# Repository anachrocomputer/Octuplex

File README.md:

# Octuplex #

A 6502/6809 microcomputer in the shape of an octagon.

## Microprocessor ##

A choice of two classic 8-bit CPUs, the 6502 or the 6809.
The two chips have similar pinouts and are placed on the PCB overlapping.
Only one chip may be installed at a time.
Clock speed 2MHz in both cases,
with the 68B09 requiring a 4x clock input,
i.e. 8MHz.
The Hitachi 63B09 may also be fitted.

## Timer ##

The standard Motorola MC6840 timer chip.
Can generate interrupts and/or PWM signals.

## Parallel I/O ##

The standard 6522 parallel port chip.
Can generate interrupts.

Two handy little circuits for additional 8-bit I/O with minimal pin count: 74LS259 and 74LS251.
The 74LS259 is an unusual chip, an addressable latch.
It takes three address input pins and a single data input pin,
and has eight output pins.
The 74LS251 is an eight-input multiplexer with tri-state output.
The selector inputs are connected to three address pins,
while the output is connected to data bit D7.
The 6502's BIT instruction can read D7 directly into the sign flag,
which can be followed by BMI or BPL.

## Analog I/O ##

The classic Ferranti ZN428 8-bit DAC chip.

The classic Ferranti ZN448 b-bit ADC chip.
Although I'm not sure about this one due to its need for a negative supply rail.

## I2C Bus ##

Classic Philips PCF8584 I2C bus controller.
Can generate interrupts.

## Async Serial I/O ##

Rockwell R65C52 dual ACIA.
Can generate interrupts.

Motorola MC6850 with optocoupler for MIDI.
Can generate interrupts.

## Display ##

TBD, most likely an LED starburst display of some kind.

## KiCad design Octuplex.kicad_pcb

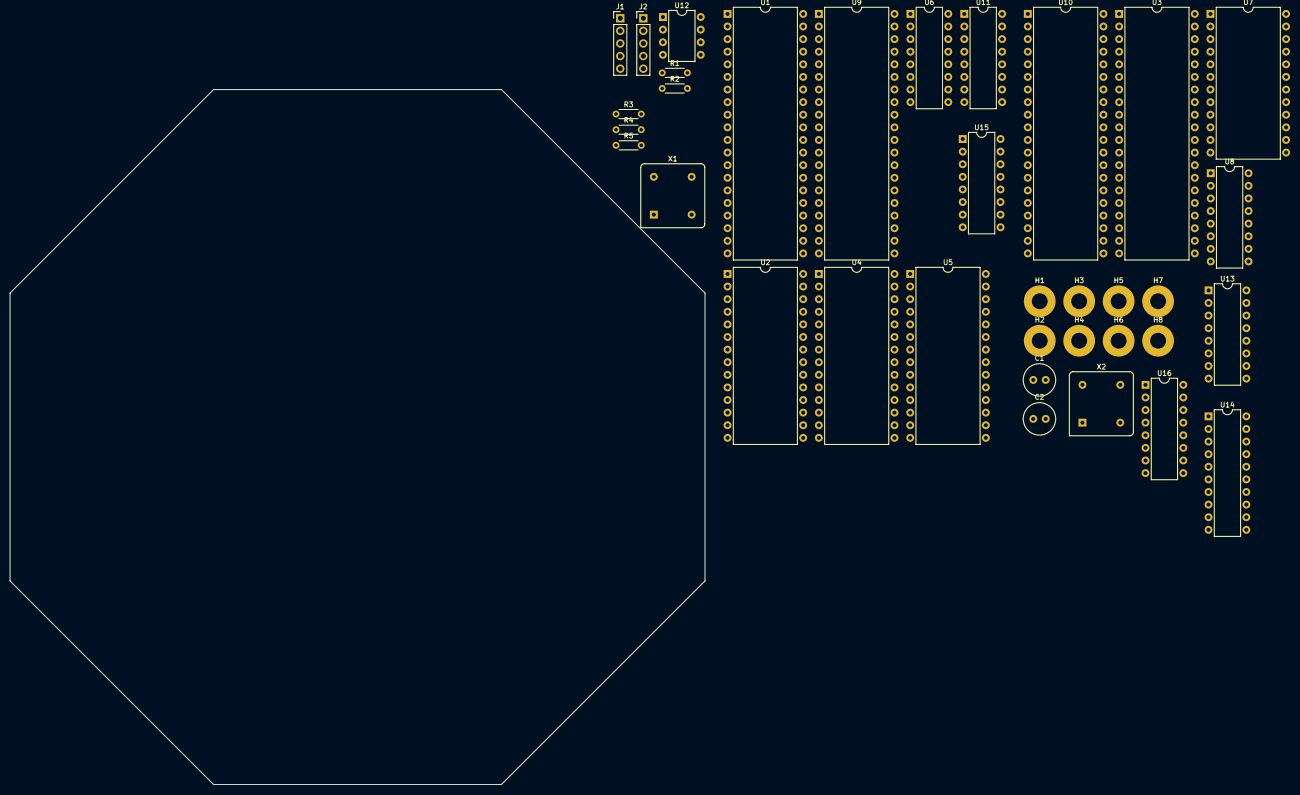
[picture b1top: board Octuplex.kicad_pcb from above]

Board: 2 copper layers, 140.0 x 140.0 mm, 35 parts (0 on the bottom side), 44 nets, no tracks yet.

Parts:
C1, C2: 0.1uF; C_Radial_D6.3mm_H5.0mm_P2.50mm
H1, H2, H3, H4, H5, H6, H7, H8: MountingHole_Pad; MountingHole_3.2mm_M3_Pad
J1, J2: DIN-5_180degree; PinHeader_1x05_P2.54mm_Vertical
R1: 220; R_Axial_DIN0204_L3.6mm_D1.6mm_P5.08mm_Horizontal
R2: 280; R_Axial_DIN0204_L3.6mm_D1.6mm_P5.08mm_Horizontal
R3, R4, R5: 10k; R_Axial_DIN0204_L3.6mm_D1.6mm_P5.08mm_Horizontal
U1: MC68B09; DIP-40_W15.24mm
U2: MC68B40; DIP-28_W15.24mm
U3: R65C52; DIP-40_W15.24mm
U4: 27128; DIP-28_W15.24mm
U5: HM62256BLP; DIP-28_W15.24mm
U6: 74LS139; DIP-16_W7.62mm
U7: MC68B50; DIP-24_W15.24mm
U8: 74LS259; DIP-16_W7.62mm
U9: M6502; DIP-40_W15.24mm
U10: R6522; DIP-40_W15.24mm
U11, U15: 74LS138; DIP-16_W7.62mm
U12: HCPL-2631; DIP-8_W7.62mm
U13: 74LS251; DIP-16_W7.62mm
U14: PCF8584; DIP-20_W7.62mm
U16: ZN428; DIP-16_W7.62mm
X1, X2: CXO_DIP8; Oscillator_DIP-8

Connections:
/E: U1.34 (E), U2.17 (E), U6.3 (A1), U7.14 (E), U9.39 (E), U10.25 (E), U11.6 (E3)
/Microprocessor/~IOSEL: U6.10 (O2), U11.4 (E1), U15.4 (E1)
/Microprocessor/~ROMCS: U4.20 (~CE), U6.9 (O3)
/Microprocessor/~TIMERCS: U2.15 (~CS0), U15.15 (O0)
/R/~W: U1.32 (R/~W), U2.13 (R/~W), U3.38 (R/~W), U6.2 (A0), U7.13 (R/~W), U9.34 (R/~W), U10.22 (R/~W), U11.1 (A0)
/a0: U1.8 (A0), U2.10 (RS0), U3.35 (RS0), U4.10 (A0), U5.10 (A0), U7.11 (RS), U8.1 (A0), U9.9 (A0), U10.38 (RS0), U13.11 (S0), U14.6 (A0)
/a1: U1.9 (A1), U2.11 (RS1), U3.36 (RS1), U4.9 (A1), U5.9 (A1), U8.2 (A1), U9.10 (A1), U10.37 (RS1), U13.10 (S1)
/a2: U1.10 (A2), U2.12 (RS2), U3.37 (RS2), U4.8 (A2), U5.8 (A2), U8.3 (A2), U9.11 (A2), U10.36 (RS2), U13.9 (S2)
/a3: U1.11 (A3), U4.7 (A3), U5.7 (A3), U9.12 (A3), U10.35 (RS3)
/a4: U1.12 (A4), U4.6 (A4), U5.6 (A4), U9.13 (A4)
/a5: U1.13 (A5), U4.5 (A5), U5.5 (A5), U9.14 (A5)
/a6: U1.14 (A6), U4.4 (A6), U5.4 (A6), U9.15 (A6)
/a7: U1.15 (A7), U4.3 (A7), U5.3 (A7), U9.16 (A7)
/a8: U1.16 (A8), U4.25 (A8), U5.25 (A8), U9.17 (A8)
/a9: U1.17 (A9), U4.24 (A9), U5.24 (A9), U9.18 (A9)
/a10: U1.18 (A10), U4.21 (A10), U5.21 (A10), U9.19 (A10), U15.1 (A0)
/a11: U1.19 (A11), U4.23 (A11), U5.23 (A11), U9.20 (A11), U11.2 (A1), U15.2 (A1)
/a12: U1.20 (A12), U4.2 (A12), U5.2 (A12), U9.22 (A12), U11.3 (A2), U15.3 (A2)
/a13: U1.21 (A13), U4.26 (A13), U5.26 (A13), U9.23 (A13), U11.5 (E2), U15.6 (E3)
/a14: U1.22 (A14), U5.1 (A14), U6.14 (A0), U9.24 (A14)
/a15: U1.23 (A15), U5.20 (~CS), U6.13 (A1), U9.25 (A15)
/d0: U1.31 (D0), U2.25 (D0), U3.24 (D0), U4.11 (D0), U5.11 (Q0), U7.22 (D0), U9.33 (D0), U10.33 (D0), U14.7 (D0), U16.2 (D0)
/d1: U1.30 (D1), U2.24 (D1), U3.23 (D1), U4.12 (D1), U5.12 (Q1), U7.21 (D1), U9.32 (D1), U10.32 (D1), U14.8 (D1), U16.1 (D1)
/d2: U1.29 (D2), U2.23 (D2), U3.22 (D2), U4.13 (D2), U5.13 (Q2), U7.20 (D2), U9.31 (D2), U10.31 (D2), U14.9 (D2), U16.16 (D2)
/d3: U1.28 (D3), U2.22 (D3), U3.21 (D3), U4.15 (D3), U5.15 (Q3), U7.19 (D3), U9.30 (D3), U10.30 (D3), U14.11 (D3), U16.15 (D3)
/d4: U1.27 (D4), U2.21 (D4), U3.19 (D4), U4.16 (D4), U5.16 (Q4), U7.18 (D4), U9.29 (D4), U10.29 (D4), U14.12 (D4), U16.14 (D4)
/d5: U1.26 (D5), U2.20 (D5), U3.18 (D5), U4.17 (D5), U5.17 (Q5), U7.17 (D5), U9.28 (D5), U10.28 (D5), U14.13 (D5), U16.13 (D5)
/d6: U1.25 (D6), U2.19 (D6), U3.17 (D6), U4.18 (D6), U5.18 (Q6), U7.16 (D6), U9.27 (D6), U10.27 (D6), U14.14 (D6), U16.12 (D6)
/d7: U1.24 (D7), U2.18 (D7), U3.16 (D7), U4.19 (D7), U5.19 (Q7), U7.15 (D7), U9.26 (D7), U10.26 (D7), U13.5 (Y), U14.15 (D7), U16.11 (D7)
/~IRQ: U1.3 (~IRQ), U2.9 (~IRQ), U3.11 (~IRQ2), U3.29 (~IRQ1), U7.7 (~IRQ), U9.4 (~IRQ), U10.21 (~IRQ), U14.5 (~INT)
/~NMI: U1.2 (~NMI), U9.6 (~NMI)
/~RD: U4.22 (~OE), U5.22 (~OE), U6.7 (O3), U14.16 (~RD)
/~RESET: R3.2, U1.37 (~RESET), U2.8 (~RESET), U3.1 (~RESET), U8.15 (Clr), U9.40 (~RESET), U10.34 (~RESET), U14.19 (~RST)
/~WR: U5.27 (~WE), U6.6 (O2), U14.18 (~WR)
GND: C1.2, C2.2, H1.1, H2.1, H3.1, H4.1, H5.1, H6.1, H7.1, H8.1, J1.2, U1.1 (VSS), U2.1 (VSS), U3.20 (VSS), U4.14 (GND), U5.14 (GND), U6.1 (E), U6.8 (GND), U6.15 (E), U7.1 (VSS), U8.8 (GND), U9.1 (VSS), U9.21 (VSS), U10.1 (VSS), U11.8 (GND), U12.5 (GND), U13.8 (GND), U14.10 (VSS), U15.5 (E2), U15.8 (GND), U16.8 (AGND), U16.9 (DGND), X1.4 (GND), X2.4 (GND)
unnamed: J1.4, R1.2
unnamed: U1.38 (EXTAL), X1.5 (OUT)
unnamed: R4.2, U1.36 (MRDY)
unnamed: R5.2, U1.40 (~HALT)
unnamed: R1.1, U12.1 (A1)
unnamed: J1.5, U12.2 (C1)
unnamed: R2.2, U7.2 (Rx_Data), U12.7 (VO1)
unnamed: U16.6 (VREFIN), U16.7 (VREFOUT)
VCC: C1.1, C2.1, R2.1, R3.1, R4.1, R5.1, U1.7 (VCC), U2.14 (VCC), U2.16 (CS1), U3.40 (VCC), U4.28 (VCC), U5.28 (VCC), U6.16 (VCC), U7.8 (CS0), U7.10 (CS1), U7.12 (VCC), U8.16 (VCC), U9.8 (VCC), U10.20 (VCC), U10.24 (CS1), U11.16 (VCC), U12.8 (VCC), U13.16 (VCC), U14.20 (VDD), U15.16 (VCC), U16.10 (VCC), X1.8 (Vcc), X2.8 (Vcc)

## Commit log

2024-10-16 Initial commit.
    Just README and .gitignore files.
2024-10-16 Initial commit of schematic and symbols.
    Just 6809, ROM, RAM, ACIA, timer so far. Not fully connected up yet.
2024-10-17 WIP: new symbols, initial PCB.
    Add 6502 and 6522 symbols. Add mounting holes, board edge, and parts to PCB. Begin wiring up.
2024-11-24 Break up schematic into hierarchial sheets.
    Connect sheets with address and data buses. TODO: add control bus.
2024-11-24 Update schematic.
    Pull-up resistors for 6809 signals. 74LS251 mux for 8 input pins. MIDI optoisolator. Wire up 74LS139 for RD and WR. Still many unconnected pins. TODO: connect sheets with control bus.
2024-11-25 Add INTS bus, address decoder, and I2C chip.
    INTS bus carries RESET, NMI, FIRQ, and IRQ. Only RESET and IRQ used so far. Philips PCF8584 I2C interface chp added. Address decoder added based on 74LS139 and two 74LS138s. TODO: add CTRL bus with E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
2024-11-26 Add control bus.
    R/W, E, RD, WR signals from microprocessor to GPIO.
2024-11-29 Replace 6551 with R65C52 (dual ACIA).
    New symbol for R65C52 in library. Two async serial ports in one 40-pin package. But it has no 'E' input. Also remove two misconnected WR and RD pins.
2024-12-01 Add ZN428 8-bit DAC.
    Add symbol for ZN428 and place it on the GPIO page.
2024-12-01 Add description of chips to be used.
    Still not sure about the ZN448 ADC -- can we find a better one that doesn't need the negative rail and the extra input bit for READY?
2024-12-01 Add two sound chips: AY8930 and YMZ284.
    Which one to use on Octuplex? YMZ284 is much smaller but write-only. AY8930 is enhanced version of AY-3-8910 but is a larger package due to two 8-bit I/O ports that we may never use.
2025-06-11 Add badges.
